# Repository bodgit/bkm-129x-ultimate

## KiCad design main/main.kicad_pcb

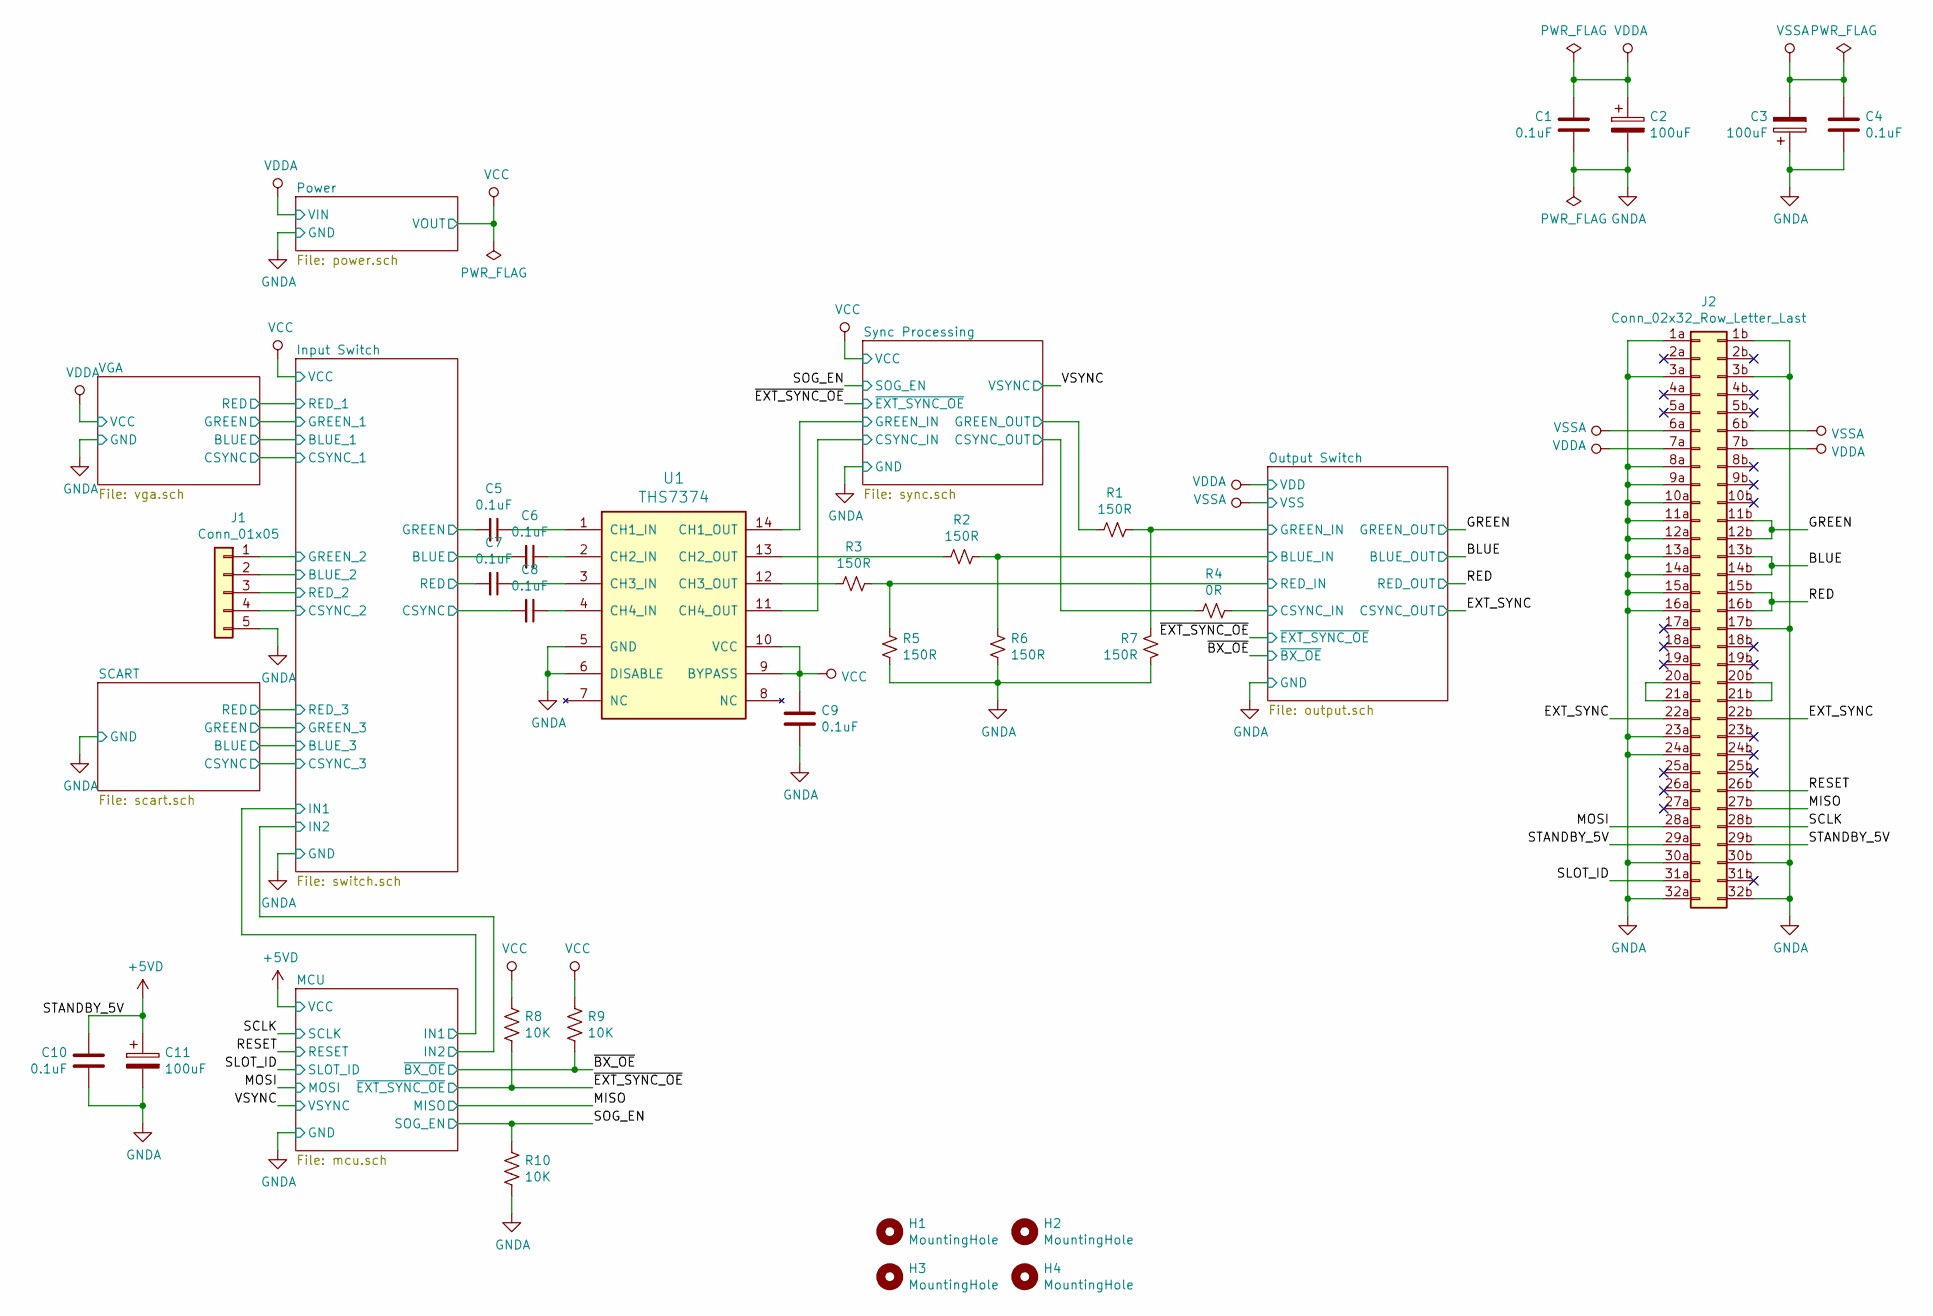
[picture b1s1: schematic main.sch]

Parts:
C1, C4, C5, C6, C7, C8, C9, C10: 0.1uF; C_0805_2012Metric_Pad1.15x1.40mm_HandSolder
C2, C3, C11: 100uF; CP_Elec_6.3x5.3
H1, H2, H3, H4: MountingHole; MountingHole_3.2mm_M3
J1: Conn_01x05; JST_NH_BS5P-SHF-1AA_1x05_P2.50mm_Horizontal
J2: Conn_02x32_Row_Letter_Last; STANDARD-PIN-64P-RA
R1, R2, R3, R5, R6, R7: 150R; R_0805_2012Metric_Pad1.15x1.40mm_HandSolder
R4: 0R; R_0805_2012Metric_Pad1.15x1.40mm_HandSolder
R8, R9, R10: 10K; R_0805_2012Metric_Pad1.15x1.40mm_HandSolder
U1: THS7374; TSSOP-14_4.4x5mm_P0.65mm

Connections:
+5VD: C10.1, C11.1, J2.29a, J2.29b; also elsewhere on the board
/BLUE: J2.13b, J2.14b; also elsewhere on the board
/EXT_SYNC: J2.22a, J2.22b; also elsewhere on the board
/GREEN: J2.11b, J2.12b; also elsewhere on the board
/Input Switch/BLUE: C6.2; also elsewhere on the board
/Input Switch/BLUE_2: J1.2; also elsewhere on the board
/Input Switch/CSYNC: C8.2; also elsewhere on the board
/Input Switch/CSYNC_2: J1.4; also elsewhere on the board
/Input Switch/GREEN: C5.2; also elsewhere on the board
/Input Switch/GREEN_2: J1.1; also elsewhere on the board
/Input Switch/RED: C7.2; also elsewhere on the board
/Input Switch/RED_2: J1.3; also elsewhere on the board
/MISO: J2.27b; also elsewhere on the board
/MOSI: J2.28a; also elsewhere on the board
/Output Switch/BLUE_IN: R2.1, R6.2; also elsewhere on the board
/Output Switch/CSYNC_IN: R4.1; also elsewhere on the board
/Output Switch/GREEN_IN: R1.1, R7.2; also elsewhere on the board
/Output Switch/RED_IN: R3.1, R5.2; also elsewhere on the board
/RED: J2.15b, J2.16b; also elsewhere on the board
/RESET: J2.26b; also elsewhere on the board
/SCLK: J2.28b; also elsewhere on the board
/SLOT_ID: J2.31a; also elsewhere on the board
/SOG_EN: R10.1; also elsewhere on the board
/Sync Processing/CSYNC_IN: U1.11 (CH4_OUT); also elsewhere on the board
/Sync Processing/CSYNC_OUT: R4.2; also elsewhere on the board
/Sync Processing/GREEN_IN: U1.14 (CH1_OUT); also elsewhere on the board
/Sync Processing/GREEN_OUT: R1.2; also elsewhere on the board
/~BX_OE: R9.2; also elsewhere on the board
/~EXT_SYNC_OE: R8.2; also elsewhere on the board
GND: C1.2, C2.2, C3.1, C4.2, C9.2, C10.2, C11.2, J1.5, J2.1a, J2.1b, J2.3a, J2.3b, J2.8a, J2.9a, J2.10a, J2.11a, J2.12a, J2.13a, J2.14a, J2.15a, J2.16a, J2.17b, J2.23a, J2.24a, J2.30a, J2.30b, J2.32a, J2.32b, R5.1, R6.1, R7.1, R10.2, U1.5 (GND), U1.6 (DISABLE); also elsewhere on the board
unnamed: C5.1, U1.1 (CH1_IN)
unnamed: C6.1, U1.2 (CH2_IN)
unnamed: C7.1, U1.3 (CH3_IN)
unnamed: C8.1, U1.4 (CH4_IN)
unnamed: J2.20a, J2.21a
unnamed: J2.20b, J2.21b
unnamed: R2.2, U1.13 (CH2_OUT)
unnamed: R3.2, U1.12 (CH3_OUT)
VCC: C9.1, R8.1, R9.1, U1.9 (BYPASS), U1.10 (VCC); also elsewhere on the board
VDDA: C1.1, C2.1, J2.7a, J2.7b; also elsewhere on the board
VSSA: C3.2, C4.1, J2.6a, J2.6b; also elsewhere on the board

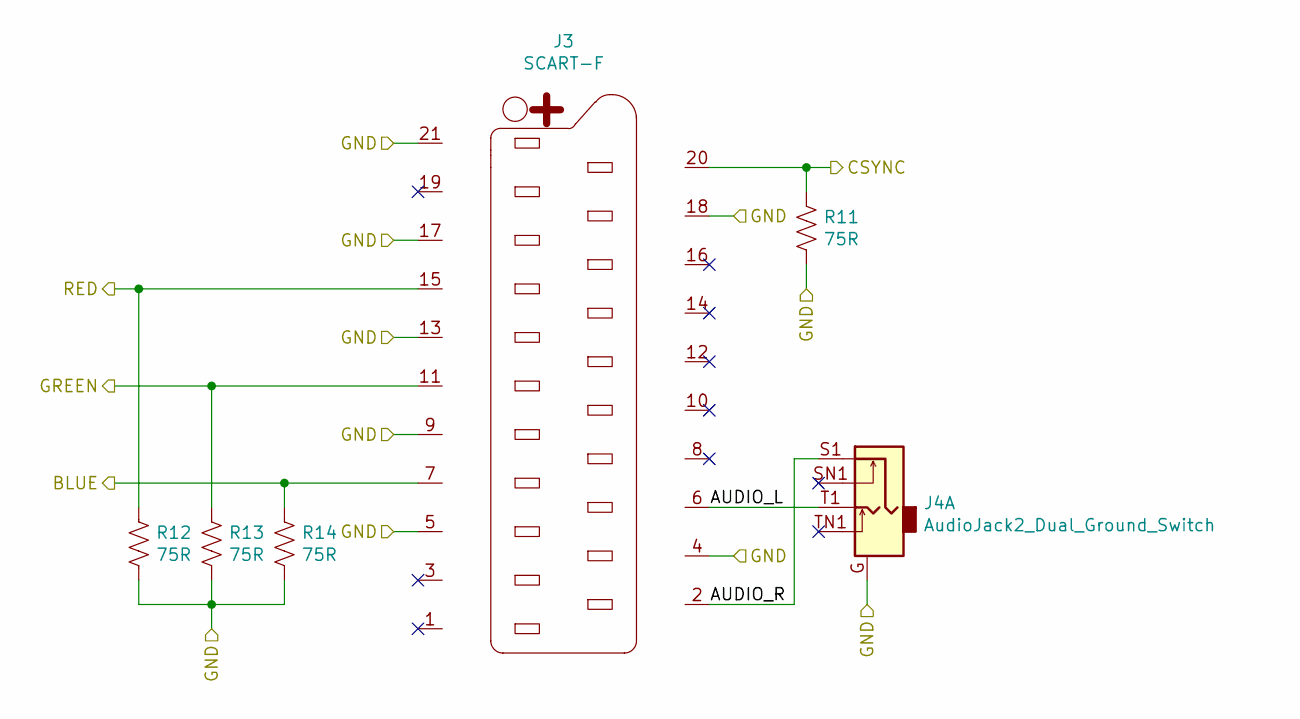
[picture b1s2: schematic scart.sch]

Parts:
J3: SCART-F; NINIGI-SCART-RA
J4: AudioJack2_Dual_Ground_Switch; SJ1-353XNG
R11, R12, R13, R14: 75R; R_0805_2012Metric_Pad1.15x1.40mm_HandSolder

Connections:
/SCART/AUDIO_L: J3.6, J4.T1
/SCART/AUDIO_R: J3.2, J4.S1
/SCART/BLUE: J3.7, R14.1; also elsewhere on the board
/SCART/CSYNC: J3.20, R11.1; also elsewhere on the board
/SCART/GREEN: J3.11, R13.1; also elsewhere on the board
/SCART/RED: J3.15, R12.1; also elsewhere on the board
GND: J3.4, J3.5, J3.9, J3.13, J3.17, J3.18, J3.21, J4.G, R11.2, R12.2, R13.2, R14.2; also elsewhere on the board

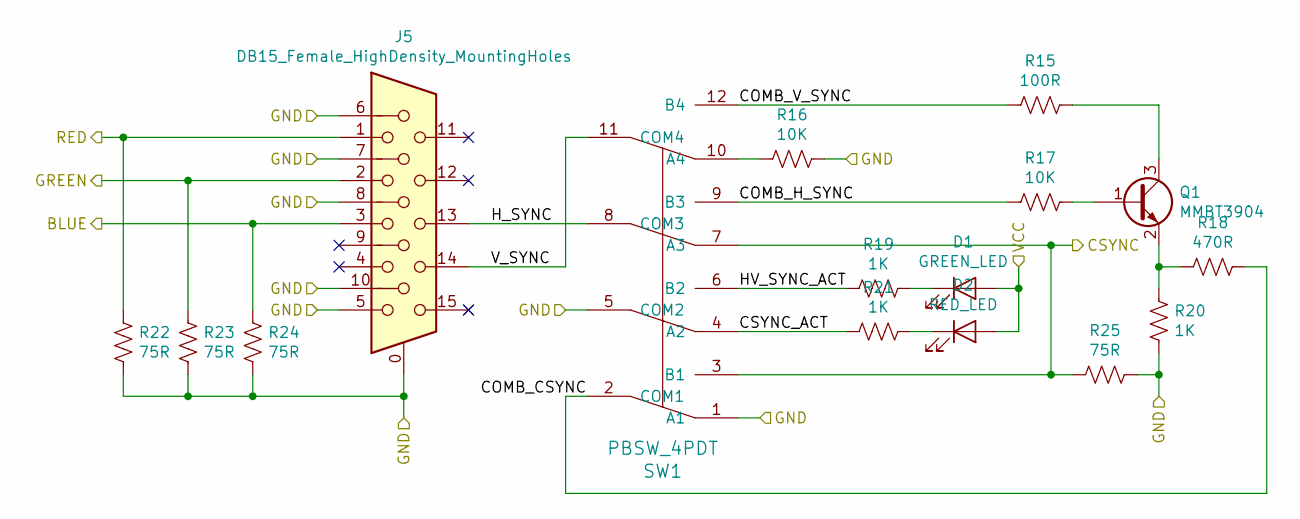
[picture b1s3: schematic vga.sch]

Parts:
D1: GREEN_LED; D_0805_2012Metric_Pad1.15x1.40mm_HandSolder
D2: RED_LED; D_0805_2012Metric_Pad1.15x1.40mm_HandSolder
J5: DB15_Female_HighDensity_MountingHoles; HD15-VGA
Q1: MMBT3904; SOT-23_Handsoldering
R15: 100R; R_0805_2012Metric_Pad1.15x1.40mm_HandSolder
R16, R17: 10K; R_0805_2012Metric_Pad1.15x1.40mm_HandSolder
R18: 470R; R_0805_2012Metric_Pad1.15x1.40mm_HandSolder
R19, R20, R21: 1K; R_0805_2012Metric_Pad1.15x1.40mm_HandSolder
R22, R23, R24, R25: 75R; R_0805_2012Metric_Pad1.15x1.40mm_HandSolder
SW1: PBSW_4PDT; PBH4U

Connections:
/VGA/BLUE: J5.3, R24.1; also elsewhere on the board
/VGA/COMB_CSYNC: R18.1, SW1.2 (COM1)
/VGA/COMB_H_SYNC: R17.2, SW1.9 (B3)
/VGA/COMB_V_SYNC: R15.2, SW1.12 (B4)
/VGA/CSYNC: R25.2, SW1.3 (B1), SW1.7 (A3); also elsewhere on the board
/VGA/CSYNC_ACT: R21.2, SW1.4 (A2)
/VGA/GREEN: J5.2, R23.1; also elsewhere on the board
/VGA/HV_SYNC_ACT: R19.2, SW1.6 (B2)
/VGA/H_SYNC: J5.13, SW1.8 (COM3)
/VGA/RED: J5.1, R22.1; also elsewhere on the board
/VGA/V_SYNC: J5.14, SW1.11 (COM4)
GND: J5.0, J5.5, J5.6, J5.7, J5.8, J5.10, R16.2, R20.2, R22.2, R23.2, R24.2, R25.1, SW1.1 (A1), SW1.5 (COM2); also elsewhere on the board
unnamed: D1.1 (K), R19.1
unnamed: D2.1 (K), R21.1
unnamed: Q1.1 (B), R17.1
unnamed: Q1.2 (E), R18.2, R20.1
unnamed: Q1.3 (C), R15.1
unnamed: R16.1, SW1.10 (A4)
VDDA: D1.2 (A), D2.2 (A); also elsewhere on the board

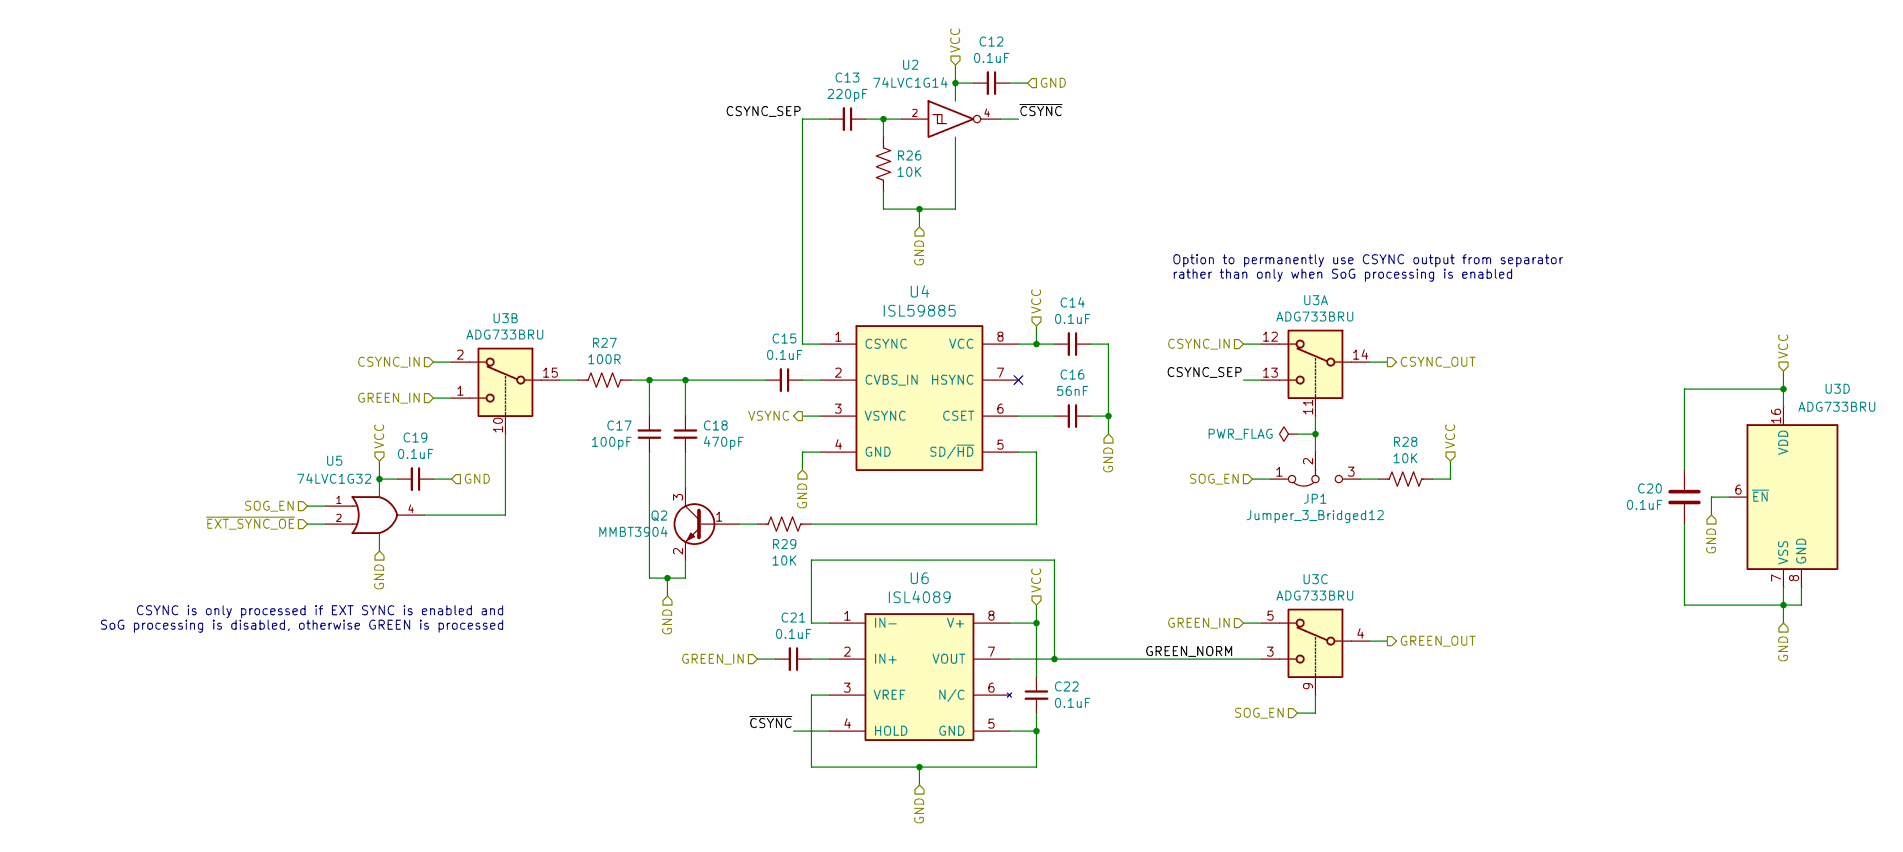
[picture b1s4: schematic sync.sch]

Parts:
C12, C14, C15, C19, C20, C21, C22: 0.1uF; C_0805_2012Metric_Pad1.15x1.40mm_HandSolder
C13: 220pF; C_0805_2012Metric_Pad1.15x1.40mm_HandSolder
C16: 56nF; C_0805_2012Metric_Pad1.15x1.40mm_HandSolder
C17: 100pF; C_0805_2012Metric_Pad1.15x1.40mm_HandSolder
C18: 470pF; C_0805_2012Metric_Pad1.15x1.40mm_HandSolder
JP1: Jumper_3_Bridged12; PinHeader_1x03_P2.54mm_Vertical
Q2: MMBT3904; SOT-23_Handsoldering
R26, R28, R29: 10K; R_0805_2012Metric_Pad1.15x1.40mm_HandSolder
R27: 100R; R_0805_2012Metric_Pad1.15x1.40mm_HandSolder
U2: 74LVC1G14; SOT-23-5_HandSoldering
U3: ADG733BRU; TSSOP-16_4.4x5mm_P0.65mm
U4: ISL59885; SOIC-8_3.9x4.9mm_P1.27mm
U5: 74LVC1G32; SOT-23-5_HandSoldering
U6: ISL4089; SOIC-8_3.9x4.9mm_P1.27mm

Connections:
/SOG_EN: JP1.1 (A), U3.9, U5.1; also elsewhere on the board
/Sync Processing/CSYNC_IN: U3.2, U3.12; also elsewhere on the board
/Sync Processing/CSYNC_OUT: U3.14; also elsewhere on the board
/Sync Processing/CSYNC_SEP: C13.2, U3.13, U4.1 (CSYNC)
/Sync Processing/GREEN_IN: C21.2, U3.1, U3.5; also elsewhere on the board
/Sync Processing/GREEN_NORM: U3.3, U6.1 (IN-), U6.7 (VOUT)
/Sync Processing/GREEN_OUT: U3.4; also elsewhere on the board
/Sync Processing/~CSYNC: U2.4, U6.4 (HOLD)
/VSYNC: U4.3 (VSYNC); also elsewhere on the board
/~EXT_SYNC_OE: U5.2; also elsewhere on the board
GND: C12.1, C14.1, C16.1, C17.1, C19.1, C20.2, C22.2, Q2.2 (E), R26.2, U2.3 (GND), U3.6 (~EN), U3.7 (VSS), U3.8 (GND), U4.4 (GND), U5.3 (GND), U6.3 (VREF), U6.5 (GND); also elsewhere on the board
unnamed: C13.1, R26.1, U2.2
unnamed: C15.1, U4.2 (CVBS_IN)
unnamed: C15.2, C17.2, C18.1, R27.1
unnamed: C16.2, U4.6 (CSET)
unnamed: C18.2, Q2.3 (C)
unnamed: C21.1, U6.2 (IN+)
unnamed: JP1.2 (C), U3.11
unnamed: JP1.3 (B), R28.2
unnamed: Q2.1 (B), R29.2
unnamed: R27.2, U3.15
unnamed: R29.1, U4.5 (SD/~HD)
unnamed: U3.10, U5.4
VCC: C12.2, C14.2, C19.2, C20.1, C22.1, R28.1, U2.5 (VCC), U3.16 (VDD), U4.8 (VCC), U5.5 (VCC), U6.8 (V+); also elsewhere on the board

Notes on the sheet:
CSYNC is only processed if EXT SYNC is enabled and SoG processing is disabled, otherwise GREEN is processed
Option to permanently use CSYNC output from separator rather than only when SoG processing is enabled

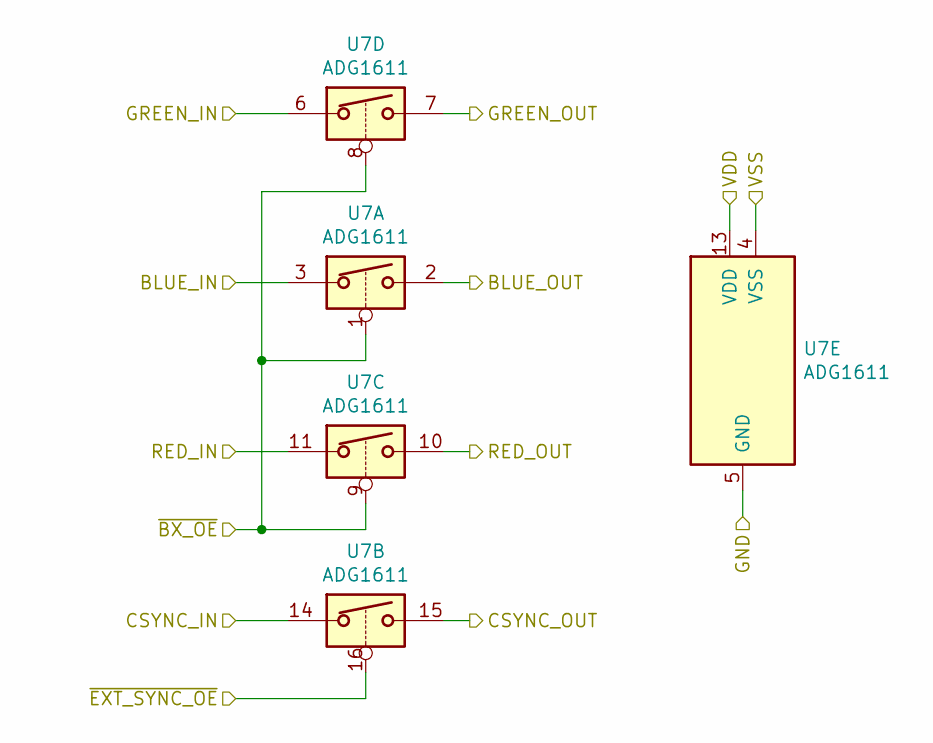
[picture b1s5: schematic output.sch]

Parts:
U7: ADG1611; TSSOP-16_4.4x5mm_P0.65mm

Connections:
/BLUE: U7.2; also elsewhere on the board
/EXT_SYNC: U7.15; also elsewhere on the board
/GREEN: U7.7; also elsewhere on the board
/Output Switch/BLUE_IN: U7.3; also elsewhere on the board
/Output Switch/CSYNC_IN: U7.14; also elsewhere on the board
/Output Switch/GREEN_IN: U7.6; also elsewhere on the board
/Output Switch/RED_IN: U7.11; also elsewhere on the board
/RED: U7.10; also elsewhere on the board
/~BX_OE: U7.1, U7.8, U7.9; also elsewhere on the board
/~EXT_SYNC_OE: U7.16; also elsewhere on the board
GND: U7.5 (GND); also elsewhere on the board
VDDA: U7.13 (VDD); also elsewhere on the board
VSSA: U7.4 (VSS); also elsewhere on the board

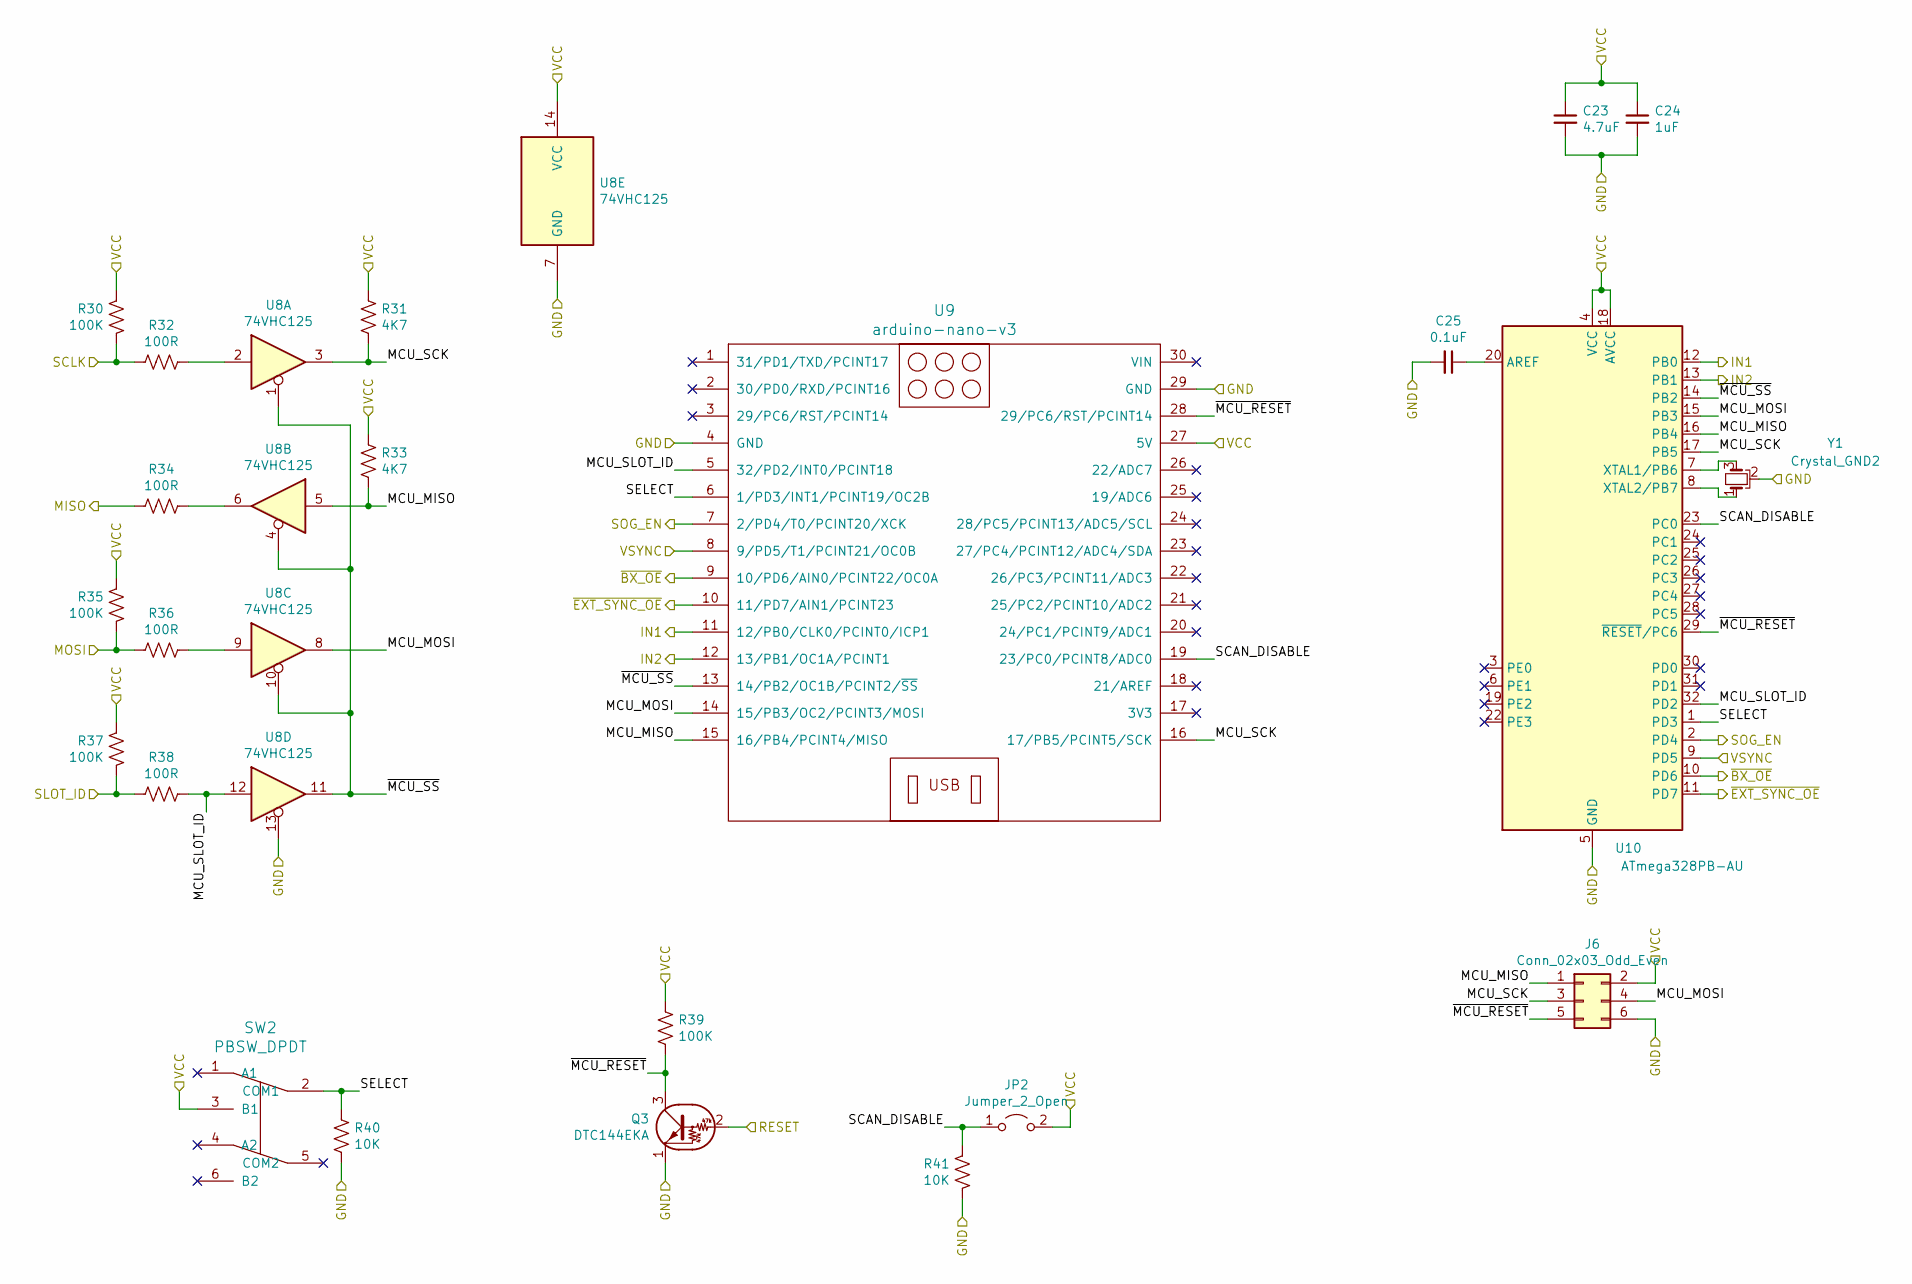
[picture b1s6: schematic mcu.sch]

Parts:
C23: 4.7uF; C_0805_2012Metric_Pad1.15x1.40mm_HandSolder
C24: 1uF; C_0805_2012Metric_Pad1.15x1.40mm_HandSolder
C25: 0.1uF; C_0805_2012Metric_Pad1.15x1.40mm_HandSolder
J6: Conn_02x03_Odd_Even; PinHeader_2x03_P2.54mm_Vertical
JP2: Jumper_2_Open; PinHeader_1x02_P2.54mm_Vertical
Q3: DTC144EKA; SC-59_Handsoldering
R30, R35, R37, R39: 100K; R_0805_2012Metric_Pad1.15x1.40mm_HandSolder
R31, R33: 4K7; R_0805_2012Metric_Pad1.15x1.40mm_HandSolder
R32, R34, R36, R38: 100R; R_0805_2012Metric_Pad1.15x1.40mm_HandSolder
R40, R41: 10K; R_0805_2012Metric_Pad1.15x1.40mm_HandSolder
SW2: PBSW_DPDT; PBH2U
U8: 74VHC125; TSSOP-14_4.4x5mm_P0.65mm
U9: arduino-nano-v3
U10: ATmega328PB-AU; TQFP-32_7x7mm_P0.8mm
Y1: Crystal_GND2; Resonator_SMD_muRata_CSTxExxV-3Pin_3.0x1.1mm

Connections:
+5VD: C23.1, C24.1, J6.2, JP2.2 (B), R30.2, R31.1, R33.1, R35.2, R37.2, R39.1, SW2.3 (B1), U8.14 (VCC), U9.27 (5V), U10.4 (VCC), U10.18 (AVCC); also elsewhere on the board
/Input Switch/IN1: U9.11 (12/PB0/CLK0/PCINT0/ICP1), U10.12 (PB0); also elsewhere on the board
/Input Switch/IN2: U9.12 (13/PB1/OC1A/PCINT1), U10.13 (PB1); also elsewhere on the board
/MCU/MCU_MISO: J6.1, R33.2, U8.5, U9.15 (16/PB4/PCINT4/MISO), U10.16 (PB4)
/MCU/MCU_MOSI: J6.4, U8.8, U9.14 (15/PB3/OC2/PCINT3/MOSI), U10.15 (PB3)
/MCU/MCU_SCK: J6.3, R31.2, U8.3, U9.16 (17/PB5/PCINT5/SCK), U10.17 (PB5)
/MCU/MCU_SLOT_ID: R38.1, U8.12, U9.5 (32/PD2/INT0/PCINT18), U10.32 (PD2)
/MCU/SCAN_DISABLE: JP2.1 (A), R41.2, U9.19 (23/PC0/PCINT8/ADC0), U10.23 (PC0)
/MCU/SELECT: R40.1, SW2.2 (COM1), U9.6 (1/PD3/INT1/PCINT19/OC2B), U10.1 (PD3)
/MCU/~MCU_RESET: J6.5, Q3.3 (C), R39.2, U9.28 (29/PC6/RST/PCINT14), U10.29 (~RESET~/PC6)
/MCU/~MCU_SS: U8.1, U8.4, U8.10, U8.11, U9.13 (14/PB2/OC1B/PCINT2/~SS), U10.14 (PB2)
/MISO: R34.2; also elsewhere on the board
/MOSI: R35.1, R36.2; also elsewhere on the board
/RESET: Q3.2 (B); also elsewhere on the board
/SCLK: R30.1, R32.2; also elsewhere on the board
/SLOT_ID: R37.1, R38.2; also elsewhere on the board
/SOG_EN: U9.7 (2/PD4/T0/PCINT20/XCK), U10.2 (PD4); also elsewhere on the board
/VSYNC: U9.8 (9/PD5/T1/PCINT21/OC0B), U10.9 (PD5); also elsewhere on the board
/~BX_OE: U9.9 (10/PD6/AIN0/PCINT22/OC0A), U10.10 (PD6); also elsewhere on the board
/~EXT_SYNC_OE: U9.10 (11/PD7/AIN1/PCINT23), U10.11 (PD7); also elsewhere on the board
GND: C23.2, C24.2, C25.2, J6.6, Q3.1 (E), R40.2, R41.1, U8.7 (GND), U8.13, U9.4 (GND), U9.29 (GND), U10.5 (GND), U10.21 (GND), Y1.2; also elsewhere on the board
unnamed: C25.1, U10.20 (AREF)
unnamed: R32.1, U8.2
unnamed: R34.1, U8.6
unnamed: R36.1, U8.9
unnamed: U10.7 (XTAL1/PB6), Y1.3
unnamed: U10.8 (XTAL2/PB7), Y1.1

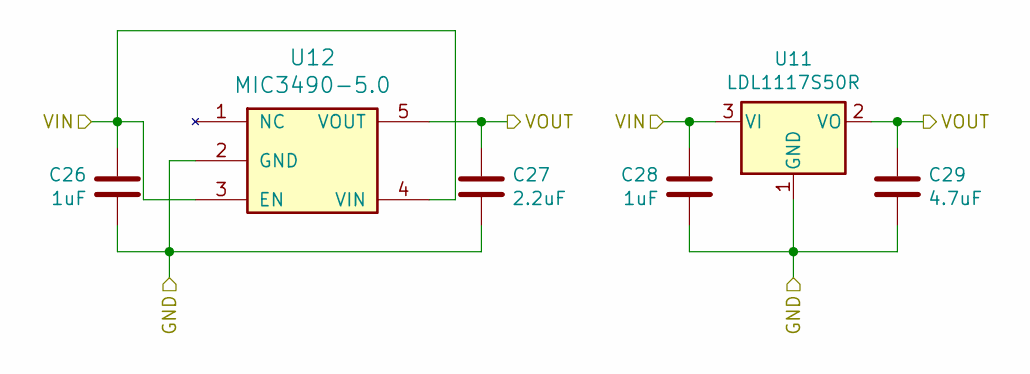
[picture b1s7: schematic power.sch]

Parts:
C26, C28: 1uF; C_0805_2012Metric_Pad1.15x1.40mm_HandSolder
C27: 2.2uF; C_0805_2012Metric_Pad1.15x1.40mm_HandSolder
C29: 4.7uF; C_0805_2012Metric_Pad1.15x1.40mm_HandSolder
U11: LDL1117S50R; SOT-223-3_TabPin2
U12: MIC3490-5.0; SOT-23-5_HandSoldering

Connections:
GND: C26.1, C27.2, C28.1, C29.2, U11.1 (GND), U12.2 (GND); also elsewhere on the board
VCC: C27.1, C29.1, U11.2 (VO), U12.5 (VOUT); also elsewhere on the board
VDDA: C26.2, C28.2, U11.3 (VI), U12.3 (EN), U12.4 (VIN); also elsewhere on the board

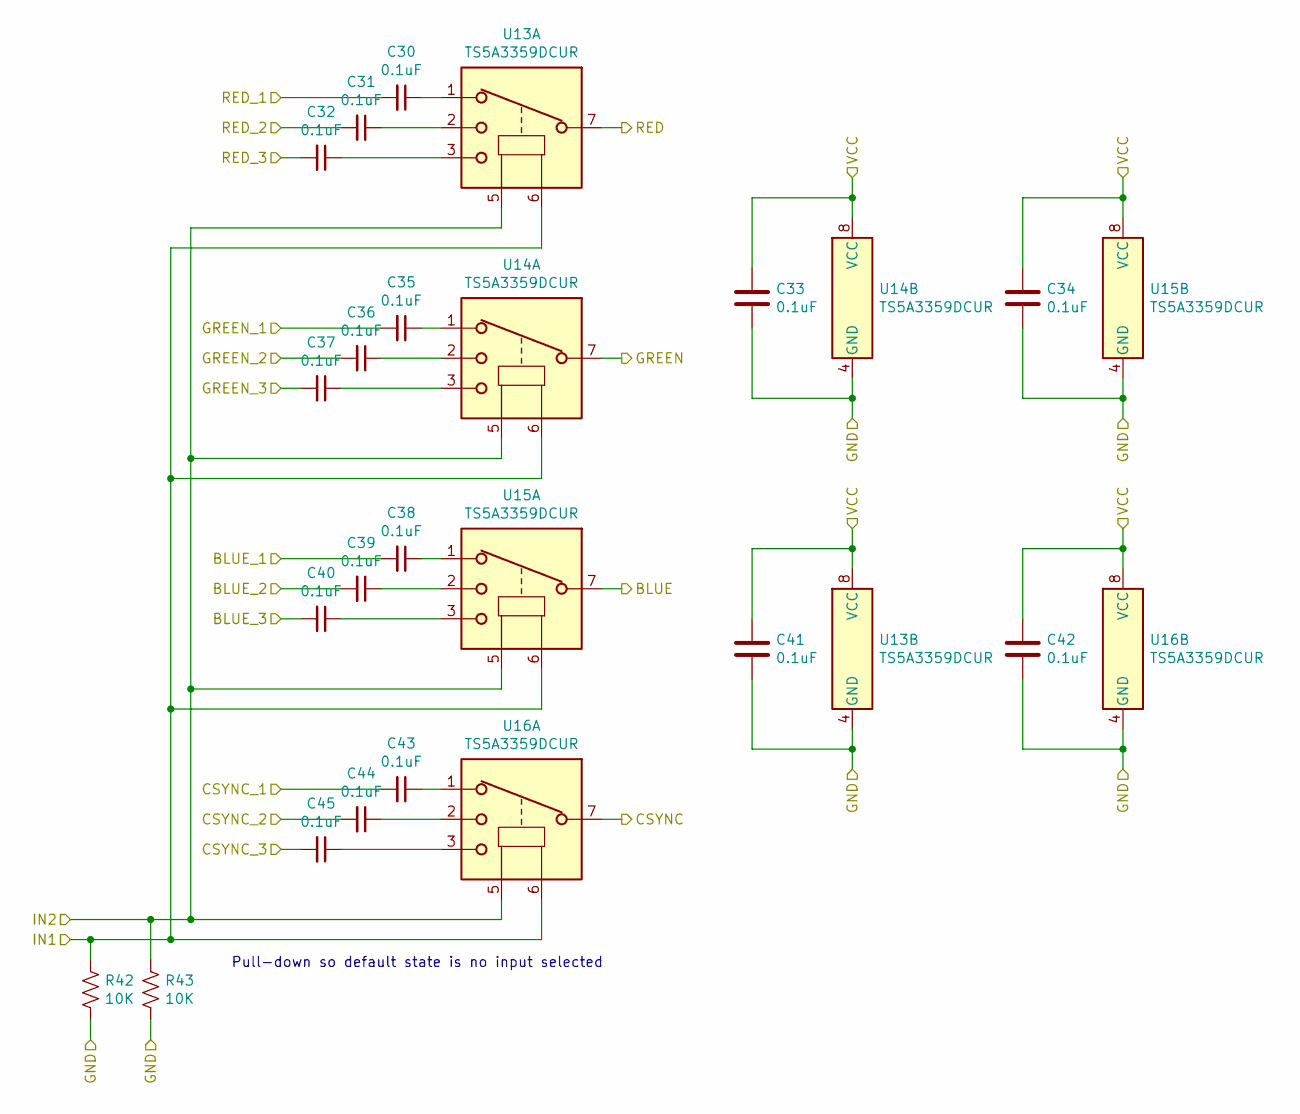
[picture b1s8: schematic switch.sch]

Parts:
C30, C31, C32, C33, C34, C35, C36, C37, C38, C39, C40, C41, C42, C43, C44, C45: 0.1uF; C_0805_2012Metric_Pad1.15x1.40mm_HandSolder
R42, R43: 10K; R_0805_2012Metric_Pad1.15x1.40mm_HandSolder
U13, U14, U15, U16: TS5A3359DCUR; VSSOP-8_2.3x2mm_P0.5mm

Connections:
/Input Switch/BLUE: U15.7; also elsewhere on the board
/Input Switch/BLUE_2: C39.2; also elsewhere on the board
/Input Switch/CSYNC: U16.7; also elsewhere on the board
/Input Switch/CSYNC_2: C44.2; also elsewhere on the board
/Input Switch/GREEN: U14.7; also elsewhere on the board
/Input Switch/GREEN_2: C36.2; also elsewhere on the board
/Input Switch/IN1: R42.1, U13.6, U14.6, U15.6, U16.6; also elsewhere on the board
/Input Switch/IN2: R43.1, U13.5, U14.5, U15.5, U16.5; also elsewhere on the board
/Input Switch/RED: U13.7; also elsewhere on the board
/Input Switch/RED_2: C31.2; also elsewhere on the board
/SCART/BLUE: C40.2; also elsewhere on the board
/SCART/CSYNC: C45.2; also elsewhere on the board
/SCART/GREEN: C37.2; also elsewhere on the board
/SCART/RED: C32.2; also elsewhere on the board
/VGA/BLUE: C38.2; also elsewhere on the board
/VGA/CSYNC: C43.2; also elsewhere on the board
/VGA/GREEN: C35.2; also elsewhere on the board
/VGA/RED: C30.2; also elsewhere on the board
GND: C33.2, C34.2, C41.2, C42.2, R42.2, R43.2, U13.4 (GND), U14.4 (GND), U15.4 (GND), U16.4 (GND); also elsewhere on the board
unnamed: C30.1, U13.1
unnamed: C31.1, U13.2
unnamed: C32.1, U13.3
unnamed: C35.1, U14.1
unnamed: C36.1, U14.2
unnamed: C37.1, U14.3
unnamed: C38.1, U15.1
unnamed: C39.1, U15.2
unnamed: C40.1, U15.3
unnamed: C43.1, U16.1
unnamed: C44.1, U16.2
unnamed: C45.1, U16.3
VCC: C33.1, C34.1, C41.1, C42.1, U13.8 (VCC), U14.8 (VCC), U15.8 (VCC), U16.8 (VCC); also elsewhere on the board

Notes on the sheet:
Pull-down so default state is no input selected

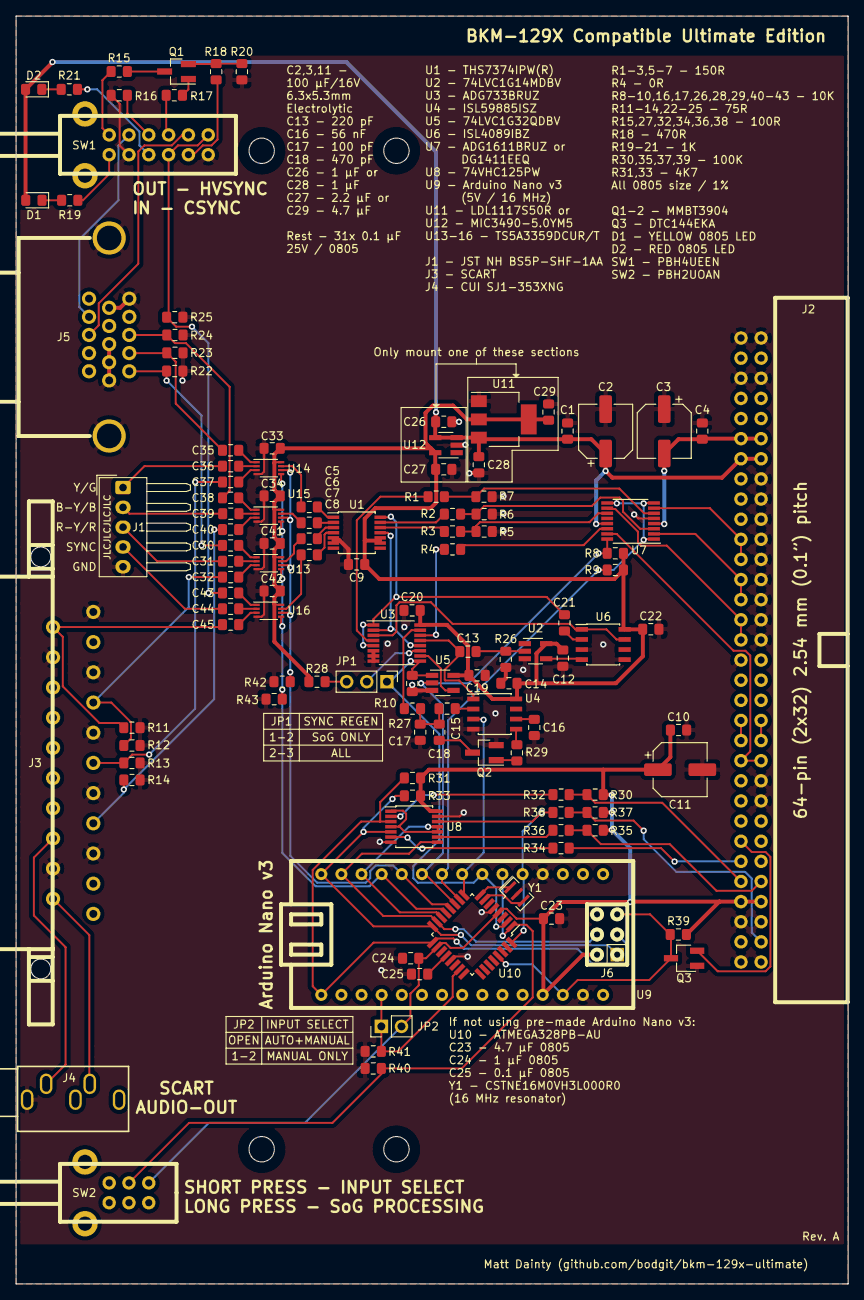
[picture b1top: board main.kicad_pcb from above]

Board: 2 copper layers, 105.0 x 160.0 mm, 124 parts (0 on the bottom side), 108 nets.

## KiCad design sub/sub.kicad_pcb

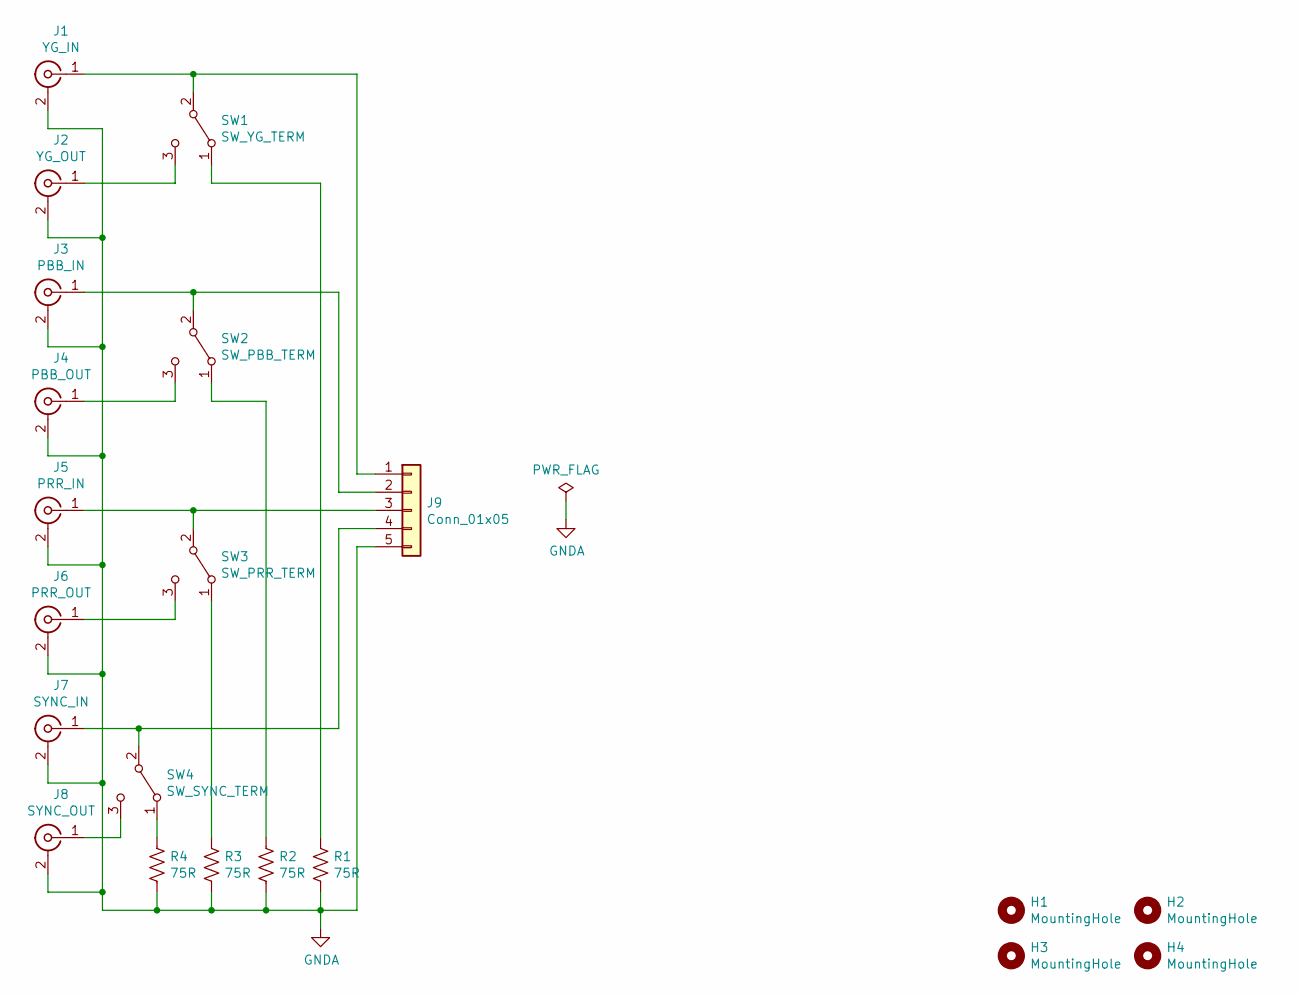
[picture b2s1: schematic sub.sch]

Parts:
H1, H2, H3, H4: MountingHole; MountingHole_3.2mm_M3
J1: YG_IN; BNC-THT
J2: YG_OUT; BNC-THT
J3: PBB_IN; BNC-THT
J4: PBB_OUT; BNC-THT
J5: PRR_IN; BNC-THT
J6: PRR_OUT; BNC-THT
J7: SYNC_IN; BNC-THT
J8: SYNC_OUT; BNC-THT
J9: Conn_01x05; JST_NH_BS5P-SHF-1AA_1x05_P2.50mm_Horizontal
R1, R2, R3, R4: 75R; R_0805_2012Metric_Pad1.15x1.40mm_HandSolder
SW1: SW_YG_TERM; js202011scqn
SW2: SW_PBB_TERM; js202011scqn
SW3: SW_PRR_TERM; js202011scqn
SW4: SW_SYNC_TERM; js202011scqn

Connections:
GNDA: J1.2 (Ext), J2.2 (Ext), J3.2 (Ext), J4.2 (Ext), J5.2 (Ext), J6.2 (Ext), J7.2 (Ext), J8.2 (Ext), J9.5, R1.2, R2.2, R3.2, R4.2
unnamed: J1.1 (In), J9.1, SW1.2 (B)
unnamed: J2.1 (In), SW1.3 (C)
unnamed: J3.1 (In), J9.2, SW2.2 (B)
unnamed: J4.1 (In), SW2.3 (C)
unnamed: J5.1 (In), J9.3, SW3.2 (B)
unnamed: J6.1 (In), SW3.3 (C)
unnamed: J7.1 (In), J9.4, SW4.2 (B)
unnamed: J8.1 (In), SW4.3 (C)
unnamed: R1.1, SW1.1 (A)
unnamed: R2.1, SW2.1 (A)
unnamed: R3.1, SW3.1 (A)
unnamed: R4.1, SW4.1 (A)

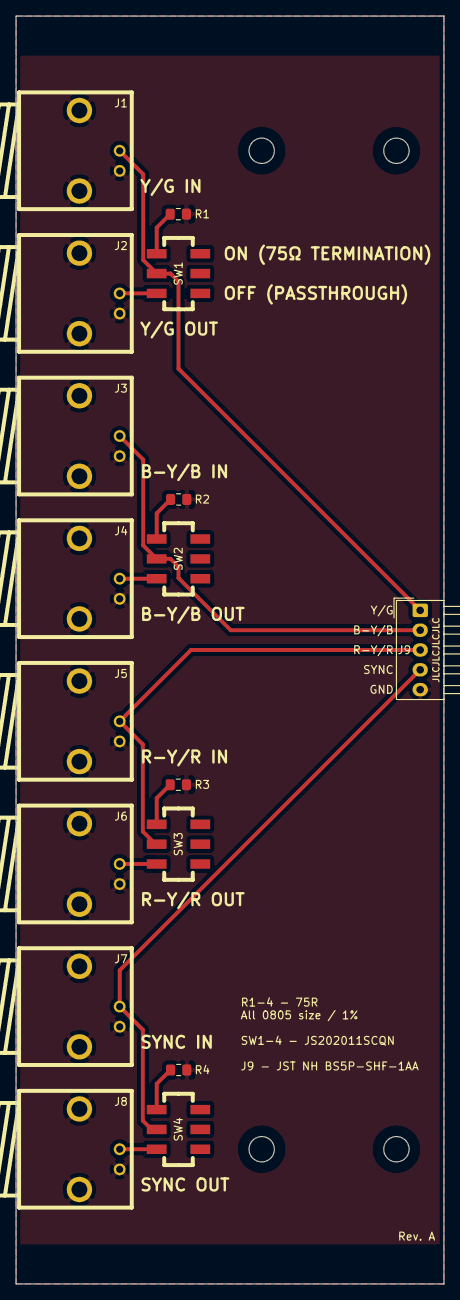
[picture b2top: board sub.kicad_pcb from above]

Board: 2 copper layers, 54.0 x 160.0 mm, 21 parts (0 on the bottom side), 13 nets.

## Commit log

2022-10-05 Add main PCB
    Also some minor tweaks.
2022-10-08 Add initial KiBot workflow
2022-10-08 Bump actions/upload-artifact from 2 to 3
    Bumps [actions/upload-artifact](https://github.com/actions/upload-artifact) from 2 to 3.
    - [Release notes](https://github.com/actions/upload-artifact/releases)
    - [Commits](https://github.com/actions/upload-artifact/compare/v2...v3)
    ---
    updated-dependencies:
    - dependency-name: actions/upload-artifact
2022-10-09 Tweak output directories
2022-10-09 Add release step to workflow
2022-10-09 Use proper mounting holes rather than edge cuts
2022-10-09 Change 74LVC125 to 74VHC125
    This particular LVC part can't be used with a 5V supply. The single gate
    LVC parts used elsewhere are fine.
2022-10-09 Cool kids give credit
2022-10-09 Add Arduino workflow steps
2022-10-09 Generate bottom silkscreen gerber
2022-12-19 Add OpenSCAD bracket model
    Generate `.stl` file for tags and add to release.
2022-12-20 Bump flat35hd99/openscad-actions from 1.3 to 1.4
    Bumps [flat35hd99/openscad-actions](https://github.com/flat35hd99/openscad-actions) from 1.3 to 1.4.
    - [Release notes](https://github.com/flat35hd99/openscad-actions/releases)
    - [Commits](https://github.com/flat35hd99/openscad-actions/compare/v1.3...v1.4)
    ---
    updated-dependencies:
    - dependency-name: flat35hd99/openscad-actions
2023-09-04 Bump actions/checkout from 3 to 4
    Bumps [actions/checkout](https://github.com/actions/checkout) from 3 to 4.
    - [Release notes](https://github.com/actions/checkout/releases)
    - [Changelog](https://github.com/actions/checkout/blob/main/CHANGELOG.md)
    - [Commits](https://github.com/actions/checkout/compare/v3...v4)
    ---
    updated-dependencies:
2023-12-15 Bump actions/upload-artifact from 3 to 4
    Bumps [actions/upload-artifact](https://github.com/actions/upload-artifact) from 3 to 4.
    - [Release notes](https://github.com/actions/upload-artifact/releases)
    - [Commits](https://github.com/actions/upload-artifact/compare/v3...v4)
    ---
    updated-dependencies:
    - dependency-name: actions/upload-artifact
2024-03-11 Bump softprops/action-gh-release from 1 to 2
    Bumps [softprops/action-gh-release](https://github.com/softprops/action-gh-release) from 1 to 2.
    - [Release notes](https://github.com/softprops/action-gh-release/releases)
    - [Changelog](https://github.com/softprops/action-gh-release/blob/master/CHANGELOG.md)
    - [Commits](https://github.com/softprops/action-gh-release/compare/v1...v2)
    ---
    updated-dependencies:
